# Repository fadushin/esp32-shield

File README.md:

This repository contains [Kicad5](https://www.kicad.org) and other files for building modular boards for ESP32 applications.

I often find that typical development boards for the ESP32 (such as the popular [Espressif ESP32 DevkitC](https://www.espressif.com/en/products/devkits/esp32-devkitc)) are great for development purposes, but sometimes less than optimal for deployment in the field.  Not only are they more expensive than they need to be, but they also contain components, such as a micro USB adapter, UART logic, and 5v voltage regulators that are not needed for 3.3v deployments (e.g., when powered off a 3.3v LiFePo4 battery) and may even detract from the power efficiency of the application.

The Kicad designs in this repository are intended to rectify some of these shortcomings, by separating the application logic from the ESP32 board itself, but in a modular way, so that you can, for example, design specific applications for your ESP32 device into which you can "plug in" your ESP32 module.  This repository also contains an adapter board for flashing the ESP32, keeping all of the micro-USB, UART, and 5v power regulation on a separate board.

The Kicad sketches in these files is designed to be pin-compatible with the common and cheap ESP32 adapter boards, which you can find on many of the on-line electronics distributors:

If you have some of these adapter boards already, you should be able to plug these modules into your design.

The sketches in this repository are designed around a board of approximate dimensions of 30.344mm x 34.620mm.  All of the boards contain two sets of 2x9 2.54mm junctions, which can be used for male pins or female headers, depending on your application.  The spacing between the center of the inner rows of these junctions is 2.54mm (1in), to be compatible with the ESP32 adapter board mentioned above.  In addition, the pin assignments for ESP32 GPIO pins is also identical to the above board.

> Note that this board is _NOT_ breadboard-friendly.

The following sketches are included in this repository.

# `esp32-wroom-shield`

The [esp32-wroom-shield](esp32-wroom-shield) sketch contains a similar design as the above adapter board, but with a few added components.

The components on this board include:

* Pads for the ESP32 WROOM module;
* Two sets of 2x9 2.54mm junctions, which can be used for pins or headers (at your discretion).  These junctions are PIN compatible with the ESP32 adapter board mentioned above.
* Two capacitors between VCC and GND;
* Pull-up resistor on EN;
* Push-button switches and capacitors for EN (`RESET`) and IO0 (`PROG`);
* Two (optional) status LEDs and resistors attached to IO2 and IO4.

This board is intended to contain a minimal set of functionality for deployment into an application.  The board may be deployed with dupont wires to connect peripherals, as needed, or may be integrated with a pin-compatible board of your own design (See the [`template`](#template) below).  All 37 GPIO pins on the ESP32 are exposed via this board.  (The one extra junction pin is mapped to GND.)

# `adafruit-cp2104-friend-adapter`

The [adafruit-cp2104-friend-adapter](adafruit-cp2104-friend-adapter) sketch contains an adapter board for integration with the [Adafruit CP2104 Friend](https://www.adafruit.com/product/3309).  This sketch can be used to connect to your ESP32 via the CP2104 USB-UART adapter onboard the Adafruit CP2104 Friend board to flash an application onto your ESP32, or for other development purposes.  The [Adafruit CP2104 Friend](https://www.adafruit.com/product/3309) can be purchased directly from Adafruit or from many parts suppliers.

This board includes:

* Two sets of 2x9 2.54mm junctions, which can be used for pins or headers (at your discretion).  These junctions are PIN compatible with the ESP32 adapter board mentioned above.
* Two sets of 1x8 2.54mm junctions, for integration with the the [Adafruit CP2104 Friend](https://www.adafruit.com/product/3309);
* AMS1117 voltage regulator and capacitors, for 3.3v power supply to the ESP32;
* A dual NPN bias transistor resistor integrated circuit, for auto-boot and auto-flash;
* A capacitor on EN to delay restart on the UART control signal;
* A power status LED connected to +5v.

# `template`

The [template](template) sketch is a template for designing your own boards for integration with the [esp32-wroom-shield](esp32-wroom-shield).

This board includes:

* Two sets of 2x9 2.54mm junctions, which can be used for pins or headers (at your discretion).  These junctions are PIN compatible with the ESP32 adapter board mentioned above.

Use this board to get started with your own design!

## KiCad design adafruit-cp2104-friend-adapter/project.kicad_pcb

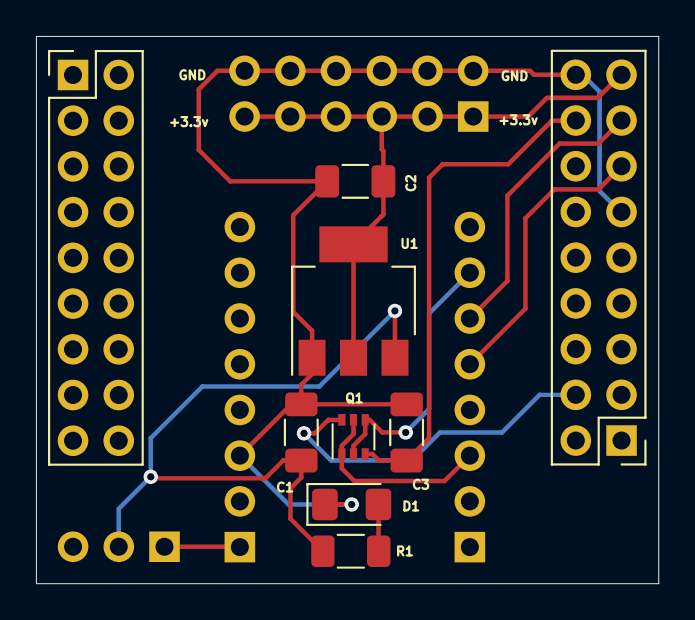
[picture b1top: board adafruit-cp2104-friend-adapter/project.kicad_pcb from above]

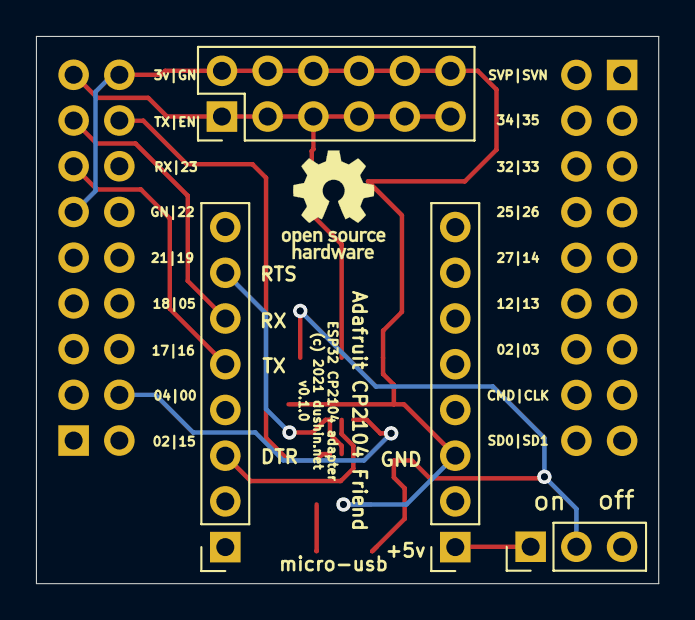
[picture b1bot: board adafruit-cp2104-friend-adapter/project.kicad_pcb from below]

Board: 2 copper layers, 34.6 x 30.4 mm, 13 parts (4 on the bottom side), 11 nets.

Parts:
C1, C2: 22uF; C_1206_3216Metric_Pad1.33x1.80mm_HandSolder
C3: 100nF; C_1206_3216Metric_Pad1.33x1.80mm_HandSolder
D1: LED; LED_1206_3216Metric_Pad1.42x1.75mm_HandSolder
J1, J2: Conn_02x09_Odd_Even; PinHeader_2x09_P2.54mm_Vertical
J3, J4: Conn_01x08_Female; PinSocket_1x08_P2.54mm_Vertical
J5: +/- rail; PinHeader_2x06_P2.54mm_Vertical
J6: Conn_01x03; PinHeader_1x03_P2.54mm_Vertical
Q1: MUN5214DW1; SOT-363_SC-70-6
R1: 2k; R_1206_3216Metric_Pad1.30x1.75mm_HandSolder
U1: AZ1117; SOT-223-3_TabPin2

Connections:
/+5v-in: J3.1, J6.1
/+5v-out: C1.1, J6.2, R1.2, U1.3
/DTR: J4.3, Q1.1, Q1.5
/EN: C3.1, J2.16, Q1.3
/ESP-RX: J2.13, J4.5
/ESP-TX: J2.15, J4.6
/GND: C1.2, C2.2, C3.2, D1.1, J2.11, J2.18, J3.3, J5.2, J5.4, J5.6, J5.8, J5.10, J5.12, U1.1
/IO0: J2.4, Q1.6
/RTS: J4.7, Q1.2, Q1.4
/VDD: C2.1, J2.17, J5.1, J5.3, J5.5, J5.7, J5.9, J5.11, U1.2
unnamed: D1.2, R1.1

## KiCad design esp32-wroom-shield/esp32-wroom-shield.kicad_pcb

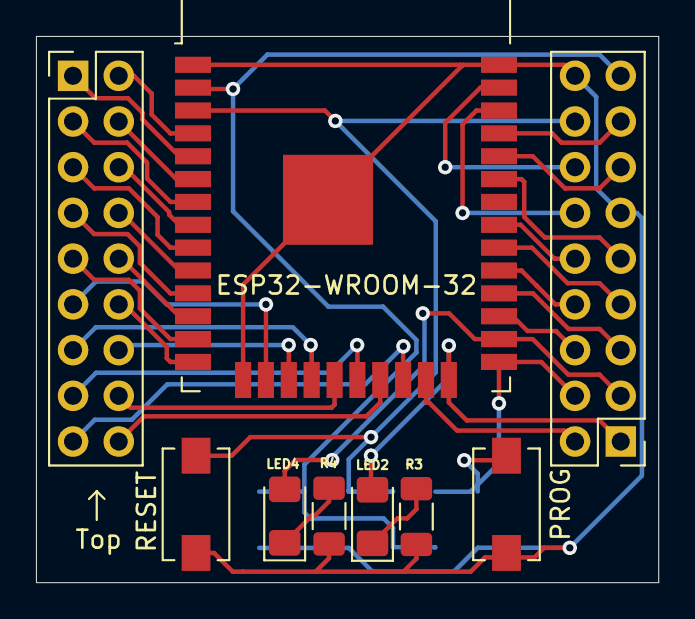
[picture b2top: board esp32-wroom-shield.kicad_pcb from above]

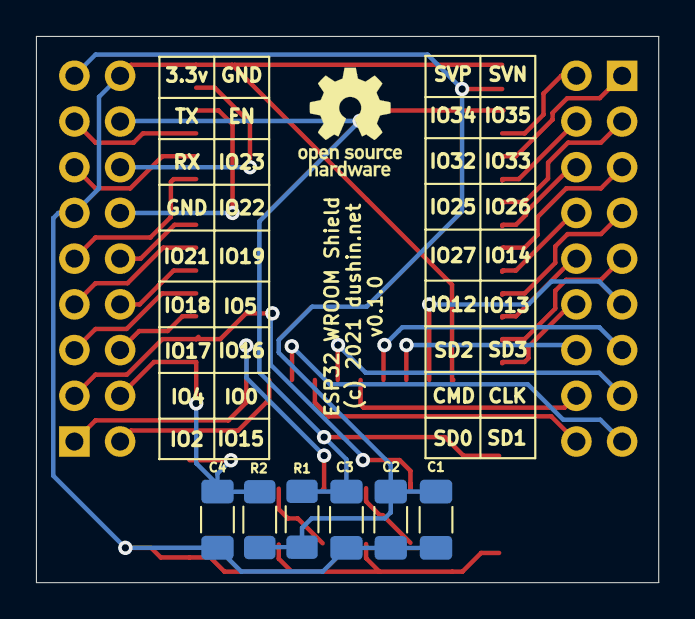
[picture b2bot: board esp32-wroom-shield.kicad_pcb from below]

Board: 2 copper layers, 34.6 x 30.3 mm, 15 parts (6 on the bottom side), 37 nets.

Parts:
C1: 22uF; C_1206_3216Metric_Pad1.33x1.80mm_HandSolder
C2, C3, C4: 0.1uF; C_1206_3216Metric_Pad1.33x1.80mm_HandSolder
D1: LED2; LED_1206_3216Metric_Pad1.42x1.75mm_HandSolder
D2: LED4; LED_1206_3216Metric_Pad1.42x1.75mm_HandSolder
J1, J2: Conn_02x09_Odd_Even; PinHeader_2x09_P2.54mm_Vertical
R1, R2: 10k; R_1206_3216Metric_Pad1.30x1.75mm_HandSolder
R3, R4: 1k; R_1206_3216Metric_Pad1.30x1.75mm_HandSolder
SW1: RESET; SW_SPST_EVQPE1
SW2: PROG; SW_SPST_EVQPE1
U1: ESP32-WROOM-32

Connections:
/CLK: J1.15, U1.20
/CMD: J1.16, U1.19
/EN: C3.1, J2.16, R1.1, SW1.2, U1.3
/IO0: C4.1, J2.4, R2.1, SW2.2, U1.25
/IO2: D1.2, J2.1, U1.24
/IO4: D2.2, J2.3, U1.26
/IO5: J2.8, U1.29
/IO12: J1.12, U1.14
/IO13: J1.11, U1.16
/IO14: J1.9, U1.13
/IO15: J2.2, U1.23
/IO16: J2.6, U1.27
/IO17: J2.5, U1.28
/IO18: J2.7, U1.30
/IO19: J2.10, U1.31
/IO21: J2.9, U1.33
/IO22: J2.12, U1.36
/IO23: J2.14, U1.37
/IO25: J1.8, U1.10
/IO26: J1.7, U1.11
/IO27: J1.10, U1.12
/IO32: J1.6, U1.8
/IO33: J1.5, U1.9
/IO34: J1.4, U1.6
/IO35: J1.3, U1.7
/RXD: J2.13, U1.34
/SD1: J1.17, U1.22
/SD2: J1.14, U1.17
/SD3: J1.13, U1.18
/SDO: J1.18, U1.21
/SVN: J1.1, U1.5
/SVP: J1.2, U1.4
/TXD: J2.15, U1.35
/VDD: C1.1, C2.1, J2.17, R1.2, R2.2, U1.2
Earth: C1.2, C2.2, C3.2, C4.2, J2.11, J2.18, R3.1, R4.1, SW1.1, SW2.1, U1.1, U1.15, U1.38, U1.39
unnamed: D1.1, R3.2
unnamed: D2.1, R4.2

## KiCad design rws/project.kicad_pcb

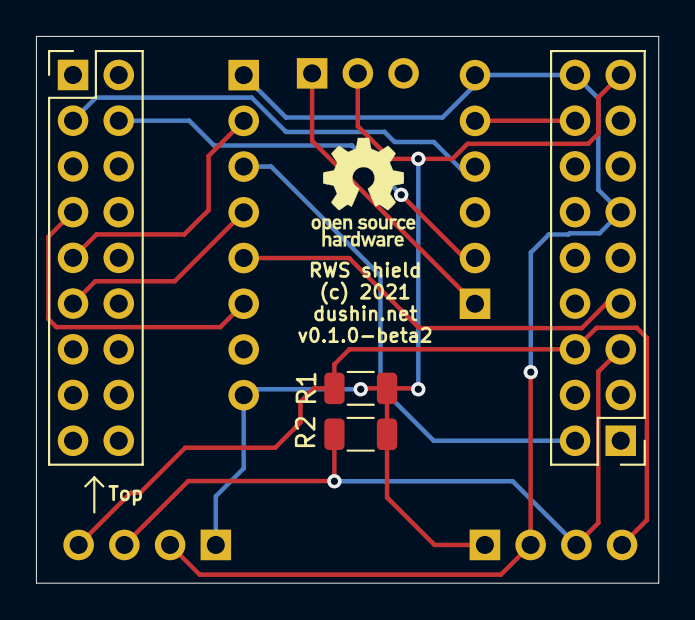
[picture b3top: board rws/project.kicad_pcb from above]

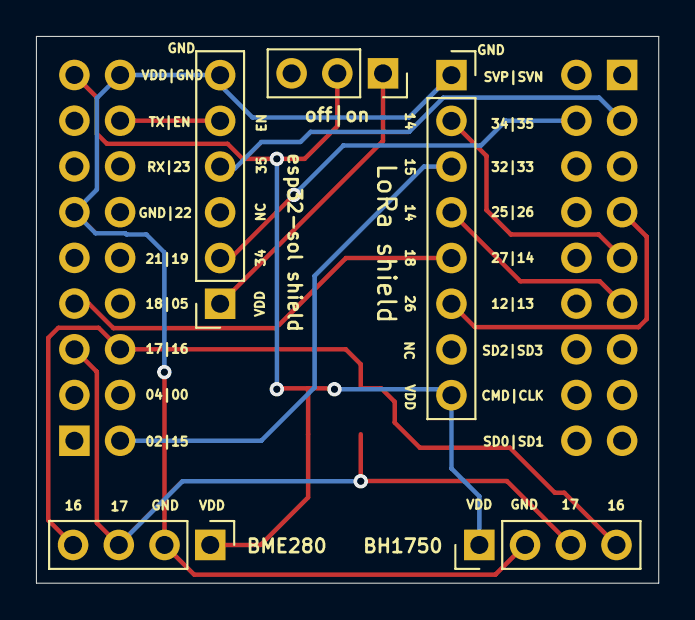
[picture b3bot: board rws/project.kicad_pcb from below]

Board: 2 copper layers, 34.6 x 30.4 mm, 9 parts (5 on the bottom side), 13 nets.

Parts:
J1, J2: Conn_02x09_Odd_Even; PinHeader_2x09_P2.54mm_Vertical
J3: BH1750; PinHeader_1x04_P2.54mm_Vertical
J4: BME280; PinHeader_1x04_P2.54mm_Vertical
J5: esp32-sol shield; PinSocket_1x06_P2.54mm_Vertical
J6: LoRa shield; PinSocket_1x08_P2.54mm_Vertical
J7: off|on; PinSocket_1x03_P2.54mm_Vertical
R1, R2: 10k; R_1206_3216Metric

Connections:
/EN: J2.16, J5.5
/GND: J2.11, J2.18, J3.2, J4.2, J5.6, J6.1
/IO13: J1.11, J6.4
/IO14: J1.9, J6.2
/IO15: J2.2, J6.3
/IO16: J2.6, J3.4, J4.4, R1.2
/IO17: J2.5, J3.3, J4.3, R2.2
/IO18: J2.7, J6.5
/IO26: J1.7, J6.6
/IO34: J1.4, J5.2
/IO35: J1.3, J5.4
/VDD: J2.17, J3.1, J4.1, J6.8, J7.2, R1.1, R2.1
/VDD-IN: J5.1, J7.1

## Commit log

2021-12-06 Fixes to beta1 versions and added rws
2021-12-13 Fixup and wiring of rws
2022-01-10 Set version to v0.1.0
2022-01-10 Moved rws project to atomvm_applications repo

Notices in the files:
adafruit-cp2104-friend-adapter/project.kicad_pcb:
(c) 2021 dushin.net
rws/project.kicad_pcb:
(c) 2021
